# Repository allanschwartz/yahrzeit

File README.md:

# Yahrzeit Project Introduction

*The operator interface and Linux appliance calculate and schedule memorial
lighting, while the embedded controller drives the physical Yahrzeit Wall.*

This repository contains the full Yahrzeit Wall system for Congregation Beth Sholom: the web appliance, scheduling logic, embedded controller firmware, LED hardware designs, and supporting documentation.

## What the project does

The system tracks memorial (Yahrzeit) records, determines when lights should be on, and sends commands to the physical wall so that the correct LEDs illuminate at the correct times.

## Repository layout

- `yahrzeit_site-v3/` — current PHP web application for viewing and editing memorial records, configuring synagogue policy, and running reports.
- `yahrzeit_site-v2/` — earlier web site implementation.
- `embedded/` — firmware and controller software for the embedded wall controller.
  - `yahrzeit_v1/` — original controller implementation.
  - `yahrzeit_v2/` — Arduino-based development work.
  - `yahrzeit_v3/` — newer controller and threading-based implementation.
- `Hardware/` — PCB and enclosure design files, schematics, and related hardware documentation.
- `panels/` — stored panel layouts and panel master assets used by the display system.
- `presentations/` — presentation materials and images related to the project.

## System overview

1. The web application stores memorial data and synagogue settings.
2. The scheduling/engine logic decides which names and panels should be lit.
3. The embedded controller receives commands and drives the LED wall.
4. The hardware layer defines the pixel boards, wiring, and panel geometry.

## Key concepts

- **Yahrzeit Wall** — the physical LED display.
- **Yahrzeit Appliance** — the software environment used by operators to manage the wall.
- **Embedded Controller** — the controller that talks to the LEDs.
- **Pixel Board / Light Engine** — the physical LED modules that make up the display.
- **Minhag / Lighting Policy** — synagogue-specific rules that determine when observances are active.

## Notes for contributors

- The current web application lives under [yahrzeit_site-v3](yahrzeit_site-v3).
- The embedded controller work is separate from the PHP appliance and should be treated as its own hardware/software subsystem.
- If you are updating documentation, prefer clear, project-level explanations that describe how the pieces fit together.

## See Also

- **Project**
  - [`./README.md`](README.md)
- **Server**
  - [`./yahrzeit_site-v3/README.md`](yahrzeit_site-v3/README.md)
  - [`./yahrzeit_site-v3/INSTALL.md`](yahrzeit_site-v3/INSTALL.md)
- **Controller**
  - [`./embedded/yahrzeit_v3/README.md`](embedded/yahrzeit_v3/README.md)
  - [`./embedded/yahrzeit_v3/INSTALL.md`](embedded/yahrzeit_v3/INSTALL.md)
- **Hardware**
  - [`./Hardware/README.md`](Hardware/README.md)

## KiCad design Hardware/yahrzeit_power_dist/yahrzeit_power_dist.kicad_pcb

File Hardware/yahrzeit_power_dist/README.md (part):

# Yahrzeit Wall 5 V Power Distribution Board

## Purpose

This board replaces the improvised low-voltage distribution wiring for one
column of the Yahrzeit Wall. One assembly accepts regulated 5 V DC from an
external power supply and distributes it to the six YYZ_PIXEL-board chains in
that column. The main input and every output branch have independent
overcurrent protection.

The complete wall has seven panel columns and therefore requires seven working
assemblies. The pricing basis is nine boards: seven for the
installed columns, and two spares onsite. Fully cabled spare assemblies remain the service objective;
final cable and power-supply quantities depend on how the spares are equipped.

This is a **direct-5 V distribution board**. The external supply, its output-voltage
adjustment, feed cable, and voltage drop under load are therefore part of the
system design.

The design is ready for prototype pricing and mechanical review, but not yet
for an unchecked production order. Complete the measurements and reviews in
[DESIGN_TODO.md](DESIGN_TODO.md) before fabrication.

## Design illustrations

*Direct-5 V input, main fuse, complementary bypass capacitors, power-present
indicator, and six independently protected outputs. Select the image to open
the PDF schematic.*

*The KiCad sources are authoritative; verify connector and cable
clearances with physical parts before release.*

## Electrical overview

- Input: regulated +5 V and GND through two-position terminal
  block J1.
- Main protection: F1 is a replaceable 7.5 A mini blade fuse in a
  PCB-mounted holder.
- Input filtering: C1 / C2 / C3 provide bulk capacitance, mid-frequency
  bypassing, and high-frequency bypassing after F1.
- Distribution: a broad +5 V copper region feeds six output branches.
- Branch protection: resettable PTC fuses F2 through F7 protect outputs J2
  through J7 independently.
- Connectors: J1 through J7 are Phoenix Contact `5442206` (BC-508X10-2 GN),
  two-position 5.08 mm-pitch PCB terminal blocks with horizontal wire entry.
  These connectors use pin 1 for +5 V and pin 2 for GND.
- Power indication: LED1 and R1 indicate that fused +5 V is present. The LED is
  advisory only and is not a safe-to-service interlock.

The front layer contains a shaped `+5V_BUS_PLANE` and a surrounding GND pour.
The back layer is a GND plane. C1, C2, and C3 straddle the +5 V/GND boundary.
The fused 5 V input feeds each branch circuit.

TP1/TP2 sit between the left mounting holes and measure input voltage.
TP3/TP4 sit between the right mounting holes and measure one of the fused output voltages.
LED1, powered through R1 from the fused 5 V rail, is labeled `POWERED`.
The indicator does not establish that all six PTC-protected outputs are live.

## Connector and cable interfaces

| Connector | Function | Pin 1 | Pin 2 |
|---|---|---|---|
| J1 | Regulated 5 V input | +5 V | GND |
| J2–J7 | Protected pixel-chain outputs | +5 V | GND |

Connector polarity must be checked against the board silkscreen, power-supply
terminals, and existing cable conductors before connection.

### J2-J7 existing output leads

Reuse the six existing cables that connect this distribution board to the six
YYZ_PIXEL board chains. At the wire nut or distribution end, cut off the obsolete
wire-nut termination and crimp on a ferrule sized for the conductor.
The [Phoenix 5442206](https://www.phoenixcontact.com/en-us/products/printed-circuit-board-terminal-bc-508x10-2-gn-5442206) specifies a 6 mm stripping length;
select a compatible ferrule and strip to its barrel length, with no exposed
conductor outside the terminal.
Keep each cable's existing pixel-board connector intact. With power disconnected,
confirm polarity with a continuity check to the pixel-board connector; retain
red for +5 V and black for GND before clamping each ferrule into J2-J7.

### J1 supply lead

J1 is a two-position screw-clamp terminal.
The supply wire is a short, approximately 24 inch, two-conductor 18 AWG feed from the
regulated 5 V supply. Terminate the supply end with ferrules compatible with
the supply's captive screw-clamp terminals; use compatible ferrules at J1
as well (four ferrules total). Prepare each end for its terminal and ferrule.
Connector J1 is
the same Phoenix terminal block as used at J2-J7.
Confirm the cable route,
length, ferrule fit, tightening torque, continuity, and polarity
before installation. Measure voltage drop under maximum load before approving
18 AWG for the final length. The power supply output is adjustable by ±10%.

## Mechanical and fabrication intent

- Board outline: 140 mm × 50 mm; outputs spaced at 20 mm centers.
- Board material: 2.0 mm FR-4; KiCad board thickness is set to 2.0 mm.
- Copper weight: 2 oz finished copper selected for the fabrication quote.
- Fabrication: two layers, green solder mask, white silkscreen, lead-free HASL.
- Mounting: four 4.5 mm mounting holes for attachment to plywood, with centers
  7.5 mm from each adjacent edge. Mount on standoffs to provide clearance beneath the PCB.
- Installation: behind each hinged wall panel, with all connectors and fuses
  accessible for service.

Before final fabrication, verify the board outline, mounting locations, hinge
clearance, connector access, fuse-removal clearance, LED visibility, and cable
bend radius with a full-size print, STEP model, or physical mockup.

## Design files

- `yahrzeit_power_dist.kicad_pro` — KiCad project
- `yahrzeit_power_dist.kicad_sch` — authoritative schematic source
- `yahrzeit_power_dist.kicad_pcb` — authoritative PCB source
- `power_dist_schematic.pdf` — schematic for reviewers without KiCad
- `power_dist_schematic.png` — README rendering of the schematic
- `yahrzeit_power_dist.PCBview.png` — saved PCB layout view
- `yahrzeit_power_dist.3Dview.png` — saved 3D view; verify current terminal
  block models and wire access against physical parts
- `yahrzeit_power_dist.pretty/` — project-specific footprints
- `enclosure/` — parametric wall enclosure and 4 × 8 box alignment jig
- `DESIGN_TODO.md` — remaining validation and release checks

## Component selection / BOM pricing

PCBWay prices are from quotation `T-V40W07135A` dated October 9, 2026,
for nine assembled boards. DigiKey prices are the unit prices in the saved
shopping cart dated October 7, 2026. Prices are per part; quantities are
extended only in the subtotal.

| Designator | Description | Manufacturer part number | Mount | Qty/board | PCBWay unit price (USD) | DigiKey cart unit price (USD) |
|---|---|---|:---:|---:|---:|---:|
| C1 | 470 µF, 25 V, 105 °C, 10,000 h low-impedance aluminum electrolytic bulk capacitor | Rubycon `25ZLH470MEFC10X12.5` | THT radial, 10 mm body, 5 mm pitch | 1 | 0.150 | 0.670 <br>[DigiKey](https://www.digikey.com/en/products/detail/rubycon/25ZLH470MEFC10X12-5/3563614) |
| C2 | 22 µF, 25 V, X7R mid-frequency ceramic bypass capacitor | Cal-Chip `GMC32X7R226K25NT` | SMD 1210 | 1 | 1.633 | 1.350 <br>[DigiKey](https://www.digikey.com/en/products/detail/cal-chip-electronics-inc/GMC32X7R226K25NT/22461278) |
| C3 | 0.1 µF, 50 V, X7R high-frequency ceramic bypass capacitor | Yageo `CC0805KRX7R9BB104` | SMD 0805 | 1 | 0.049 | 0.180 <br>[DigiKey](https://www.digikey.com/en/products/detail/yageo/CC0805KRX7R9BB104/302874?s=N4IgTCBcDaIMJwAwA5EFYDSAlAGgdiwE4AhYgRkQBYQBdAXyA) |
| F1 | 7.5 A, 32 VDC MINI automotive blade fuse | Littelfuse `029707.5WXNV` | Plug-in; purchased separately | 1 | — | 0.301 <br>[DigiKey](https://www.digikey.com/en/products/detail/littelfuse-inc/029707-5WXNV/146586) |
| F1 holder | Vertical MINI blade-fuse PCB holder | Keystone `3568` | THT | 1 | 1.174 | 1.310 <br>[DigiKey](https://www.digikey.com/en/products/detail/keystone-electronics/3568/2137306) |
| F2–F7 | Resettable PTC, 16 V, 1.5 A hold current | Littelfuse `1812L150/16DR` | SMD 1812 | 6 | 0.086 | 0.612 <br>[DigiKey](https://www.digikey.com/en/products/detail/littelfuse-inc/1812L150-16DR/3305611) |
| J1–J7 | PCB terminal block, 2-position, 5.08 mm pitch, horizontal wire entry | Phoenix Contact `5442206` (BC-508X10-2 GN) | THT | 7 | 0.276 | 0.500 est.<br>[DigiKey](https://www.digikey.com/en/products/detail/phoenix-contact/5442206/4390264) |
| LED1 | Green power-present LED | Kingbright `APT2012CGCK` | SMD 0805 | 1 | 0.140 | 0.220 <br>[DigiKey](https://www.digikey.com/en/products/detail/kingbright/APT2012CGCK/1747526) |
| R1 | 1 kΩ, 1%, 0.125 W power-indicator resistor | Yageo `RC0805FR-071KL` | SMD 0805 | 1 | 0.014 | 0.100 <br>[DigiKey](https://www.digikey.com/en/products/detail/yageo/RC0805FR-071KL/727444?s=N4IgTCBcDaIEoGEAMAOJBWAYnAtEg7AIwDSAMiALoC%2BQA) |
| **Installed PCB-component subtotal per board** | | | | | **$5.608** | **$11.002** |

PCBWay's installed-component total is $50.472 for nine boards. The plug-in
fuses are purchased separately and therefore are excluded from both
subtotals. The DigiKey cart reflects the change from Phoenix Contact `1715721`
to `5442206`.

## Extra parts for one complete column assembly

These items are outside the PCB assembly BOM. The existing six pixel-chain
cables are reused for each board; only their board-end terminations are
converted to ferrules. A short supply lead is required for each installed
assembly.

| Item | Description | Part or drawing | Qty/assembly | Unit cost (USD) |
|---|---|---|---:|---:|
| Power supply | Regulated 5 V, 10 A, 50 W adjustable enclosed supply | BTF-LIGHTING `AM50-B05-HD` ([Amazon](https://www.amazon.com/dp/B0FZQNMHN6)) | 1 | $22 |
| Input lead | Two-conductor 18 AWG supply feed, approximately 24 inches; both ends ferruled | n/a | 4 ferrules<br> 24" wire | Negligible—bulk supplies |
| Output lead preparation | Two ferrules per existing J2-J7 cable; six cables are reused | n/a | 12 ferrules | Negligible—bulk supplies |
| 3D printed case | | | | bulk supplies |
| 3mm screws  | with threaded inserts in the case | | | bulk supplies |

The PCB BOM excludes the external 5 V supply, input lead, and ferrules. Bulk and lab supplies will be roughly $50 for the total project.

*Do not release this table as a purchasing BOM until every ordering code,
footprint, voltage/current rating, temperature rating, lifecycle status, and
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
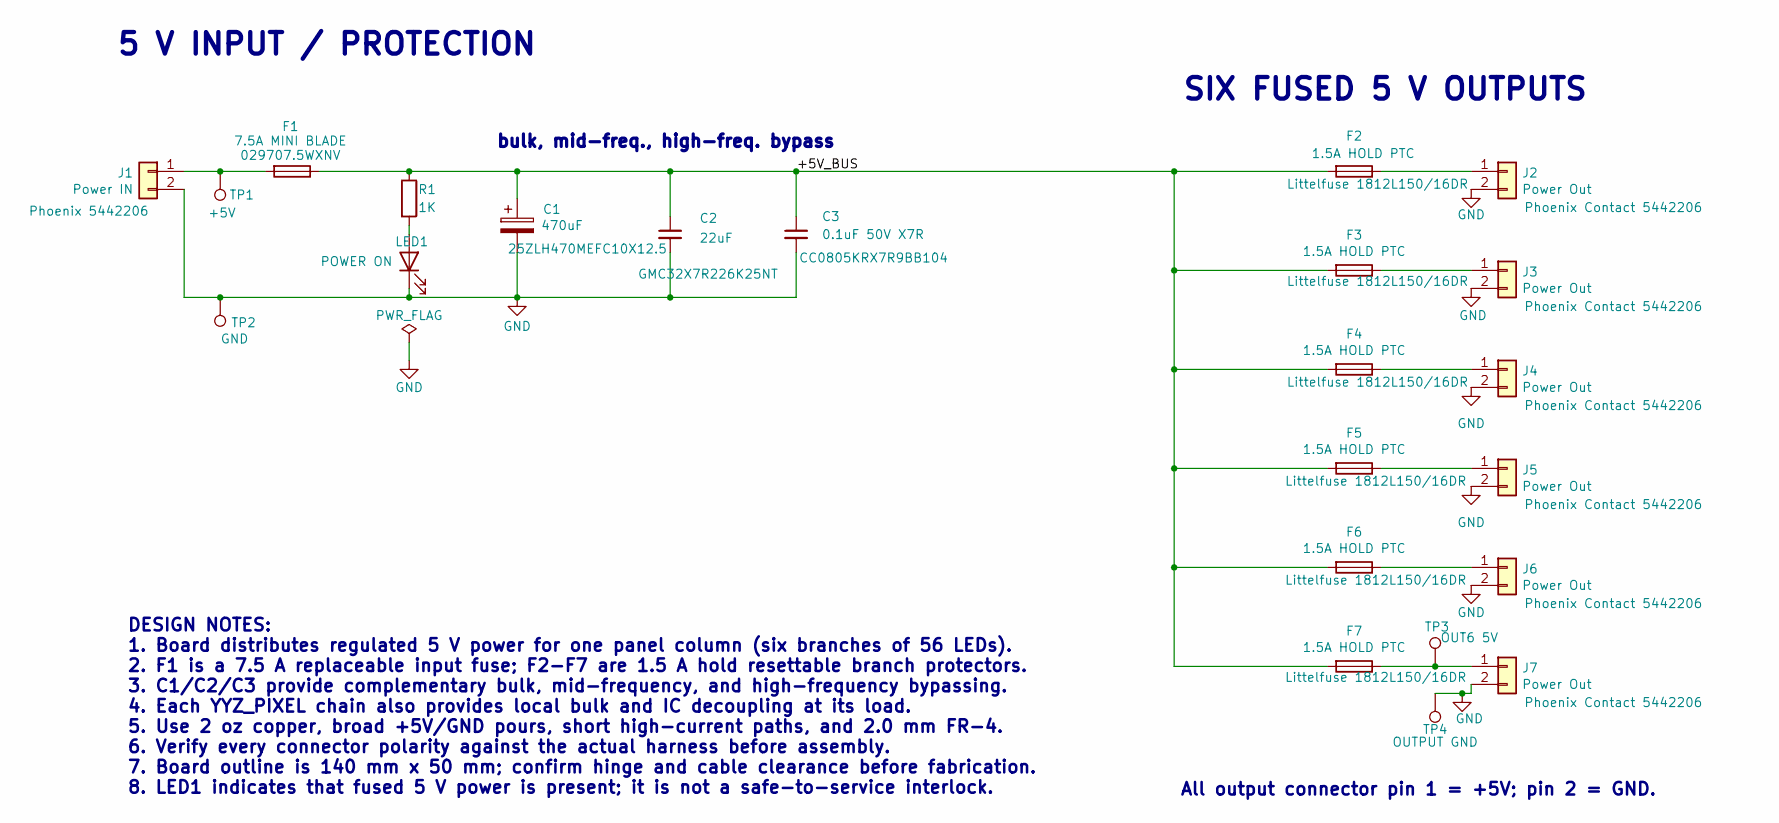
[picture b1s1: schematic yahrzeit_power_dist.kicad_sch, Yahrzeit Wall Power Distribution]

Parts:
C1: 470uF; CP_Radial_D10.0mm_P5.00mm; MPN 25ZLH470MEFC10X12.5
C2: 22uF; C_1210_3225Metric; MPN GMC32X7R226K25NT
C3: 0.1uF 50V X7R; C_0805_2012Metric; MPN CC0805KRX7R9BB104
F1: 7.5A MINI BLADE; Fuseholder_Blade_Mini_Keystone_3568; MPN 029707.5WXNV
F2, F3, F4, F5, F6, F7: 1.5A HOLD PTC; Fuse_1812_4532Metric; MPN Littelfuse 1812L150/16DR
J1: Power IN; TerminalBlock_Phoenix_BC-508X10-2_1x02_P5.08mm_Horizontal; MPN Phoenix 5442206
J2, J3, J4, J5, J6, J7: Power Out; TerminalBlock_Phoenix_BC-508X10-2_1x02_P5.08mm_Horizontal; MPN Phoenix Contact 5442206
LED1: POWER ON; LED_0805_2012Metric; MPN APT2012CGCK
R1: 1K; R_0805_2012Metric; MPN RC0805FR-071KL
TP1: +5V; TestPoint_Pad_D2.5mm; MPN PCB test pad
TP2: GND; TestPoint_Pad_D2.5mm; MPN PCB test pad
TP3: OUT6 5V; TestPoint_Pad_D2.5mm; MPN PCB test pad
TP4: OUTPUT GND; TestPoint_Pad_D2.5mm; MPN PCB test pad

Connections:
/+5V_BUS: C1.1, C2.1, C3.1, F1.1, F2.2, F3.2, F4.2, F5.2, F6.2, F7.2, R1.1
GND: C1.2, C2.2, C3.2, J1.2, J2.2, J3.2, J4.2, J5.2, J6.2, J7.2, LED1.1 (K), TP2.1 (1_1), TP4.1 (1_1)
unnamed: F1.2, J1.1, TP1.1 (1_1)
unnamed: F2.1, J2.1
unnamed: F3.1, J3.1
unnamed: F4.1, J4.1
unnamed: F5.1, J5.1
unnamed: F6.1, J6.1
unnamed: F7.1, J7.1, TP3.1 (1_1)
unnamed: LED1.2 (A), R1.2

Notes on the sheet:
SIX FUSED 5 V OUTPUTS
5 V INPUT / PROTECTION
bulk, mid-freq., high-freq. bypass
All output connector pin 1 = +5V; pin 2 = GND.
DESIGN NOTES: 1. Board distributes regulated 5 V power for one panel column (six branches of 56 LEDs). 2. F1 is a 7.5 A replaceable input fuse; F2-F7 are 1.5 A hold resettable branch protectors. 3. C1/C2/C3 provide complementary bulk, mid-frequency, and high-frequency bypassing. 4. Each YYZ_PIXEL c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

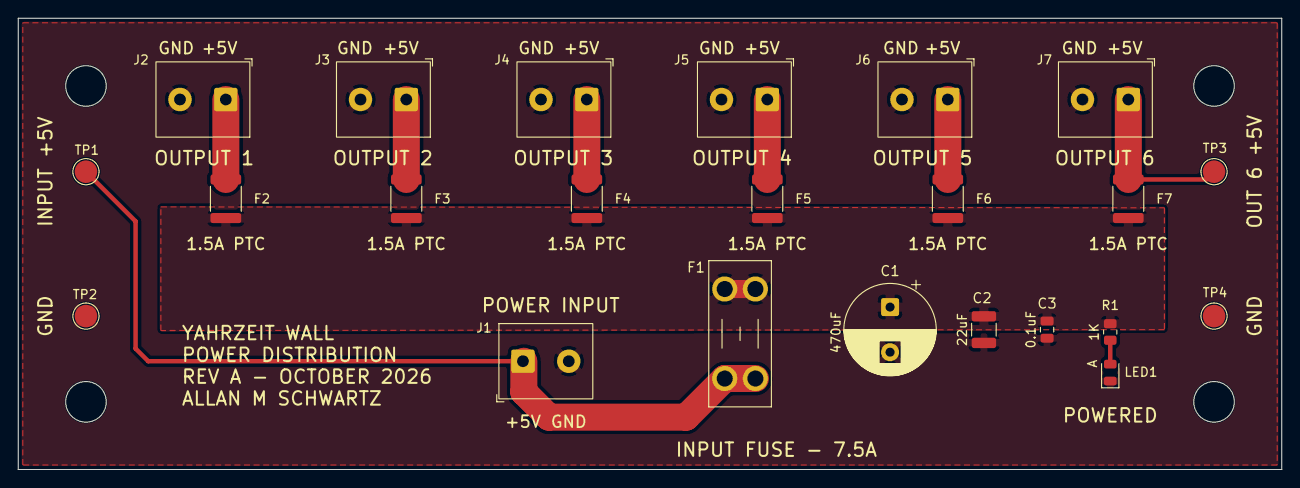
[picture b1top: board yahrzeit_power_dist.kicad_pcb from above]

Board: 2 copper layers, 140.0 x 50.0 mm, 27 parts (0 on the bottom side), 10 nets.

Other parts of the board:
H1, H2, H3, H4: MountingHole_4.5mm

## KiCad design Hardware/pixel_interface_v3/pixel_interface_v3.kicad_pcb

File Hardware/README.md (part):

# Yahrzeit Wall Hardware

This directory contains the electrical and mechanical design files for the
Yahrzeit Wall controller, interface board, pixel boards, test fixtures, and
enclosures.

The current controller uses an Arduino Uno R4, an Arduino-compatible Ethernet
shield, and the Yahrzeit Controller Pixel Interface V3 board. The interface
board connects the controller stack to the installed chain of YYZ Pixel boards.

*The bench-test fixture brings together the controller stack, Pixel Interface
board, and two nine-section YYZ Pixel boards.*

## 3D-Printed Parts

The files under [`3D Printing`](3D%20Printing/) may be browsed
online, with GitHub displaying the JPEG photographs and interactive previews of
the STL models.

### Commercial Controller Enclosure

- [arduino\_uno\_r4\_commercial\_enclosure\_vendor.jpg](3D%20Printing/arduino_uno_r4_commercial_enclosure_vendor.jpg)
  -- Vendor product photograph, saved from the Amazon listing, showing the
  commercial enclosure with an Arduino Uno R4 and an Ethernet-shield stack.

### Production Mounting Flange

The production controller uses a commercial enclosure with a custom
3D-printed flange that adapts its DIN-rail mounting feature for flat wall
mounting.

- [mount\_flange.scad](3D%20Printing/mount_flange.scad) -- Parametric OpenSCAD
  source.
- [mount\_flange.stl](3D%20Printing/mount_flange.stl) -- Printable mounting
  flange.

### Alternative Controller Enclosure

This enclosure was designed for the three-board controller stack. The
close-fitting commercial enclosure documented in the embedded-controller
installation notes is the preferred production enclosure, but this printable
design is retained as a replacement option and design reference.

- [yahrzeit\_controller\_case.scad](3D%20Printing/yahrzeit_controller_case.scad)
  -- Parametric OpenSCAD source.
- [yahrzeit\_controller\_case.stl](3D%20Printing/yahrzeit_controller_case.stl)
  -- Printable enclosure body.
- [yahrzeit\_controller\_case-cover.stl](3D%20Printing/yahrzeit_controller_case-cover.stl)
  -- enclosure cover.
- [yahrzeit\_controller\_case.jpg](3D%20Printing/yahrzeit_controller_case.jpg)
  -- Photograph of the printed enclosure body.

### Test-Fixture Plate

The fixture plate supports the small YYZ Pixel test assembly used during
controller development and bench testing.

- [fixture\_plate.scad](3D%20Printing/fixture_plate.scad) -- Parametric OpenSCAD
  source.
- [fixture\_plate.stl](3D%20Printing/fixture_plate.stl) -- Printable fixture
  plate.
- [fixture\_plate.jpg](3D%20Printing/fixture_plate.jpg) -- Photograph of the
  printed fixture plate.

## Yahrzeit Controller Pixel Interface V3

*KiCad rendering of the Yahrzeit Controller Pixel Interface V3 board.*

The current interface board adapts the Arduino controller stack to the
five-signal YYZ Pixel ribbon cable and provides the green ALIVE status LED.

- [pixel\_interface\_v3.kicad\_pro](pixel_interface_v3/pixel_interface_v3.kicad_pro)
  -- Open this project file in KiCad.
- [pixel\_interface\_v3.kicad\_sch](pixel_interface_v3/pixel_interface_v3.kicad_sch)
  -- KiCad schematic.
- [pixel\_interface\_v3.kicad\_pcb](pixel_interface_v3/pixel_interface_v3.kicad_pcb)
  -- KiCad PCB layout.
- [pixel\_interface\_v3-3D viewer.png](pixel_interface_v3/pixel_interface_v3-3D%20viewer.png)
  -- KiCad 3D rendering.
- [pixel\_interface\_v3-schematic.png](pixel_interface_v3/pixel_interface_v3-schematic.png)
  -- Schematic preview.
- [pixel\_interface\_v3\_D1\_polarity\_note.pdf](pixel_interface_v3/pixel_interface_v3_D1_polarity_note.pdf)
  -- Status-LED polarity and assembly note.

## Nine-Section YYZ Pixel Board

*KiCad rendering of the nine-section YYZ Pixel board.*

The `yahrzeit_pixel9` board combines nine complete YYZ Pixel circuits on one PCB, using the same octal bus transceiver and 8-bit shift register as the individual boards installed in the wall. A single `yahrzeit_pixel9` behaves as one complete Yahrzeit Wall panel, allowing a desktop test fixture to be constructed. Two or more yahrzeit_pixel9 boards may be chained together to emulate multiple panels.

*The reusable KiCad hierarchical sheet implements one eight-pixel YYZ Pixel
circuit. The `yahrzeit_pixel9` top-level schematic instantiates this sheet nine
times.*

- [yahrzeit\_pixel9.kicad\_pro](yahrzeit_pixel9/yahrzeit_pixel9.kicad_pro) --
  Open this project file in KiCad.
- [yahrzeit\_pixel9.kicad\_sch](yahrzeit_pixel9/yahrzeit_pixel9.kicad_sch) --
  KiCad top-level schematic.
- [pblock.kicad\_sch](yahrzeit_pixel9/pblock.kicad_sch) -- Reusable
  eight-pixel hierarchical sheet.
- [yahrzeit\_pixel9.kicad\_pcb](yahrzeit_pixel9/yahrzeit_pixel9.kicad_pcb) --
  KiCad PCB layout.
- [yahrzeit\_pixel9-schematic.pdf](yahrzeit_pixel9/yahrzeit_pixel9-schematic.pdf)
  -- multipage schematic.
- [yahrzeit\_pixel9.png](yahrzeit_pixel9/yahrzeit_pixel9.png) -- KiCad board
  rendering.

## YYZ Pixel Board V2

*Schematic of the preliminary YYZ Pixel Board V2 design.*

YYZ Pixel Board V2 is a proposed modern replacement for an individual
installed pixel board. It retains the legacy 74HC245 input buffer, 74HC595
shift register, 5 V power daisy chain, and 2x5 signal-cable interface so that
it can be evaluated with the existing wall and controller. The present
prototype provides eight LED channels. Its LED resistors intentionally use
four different values, in pairs, so brightness and current can be compared
with the original wall before a production value is selected.

This is design work in progress, not a released production board. Connector
part numbers, the final LED resistor value, cable construction, power margin,
and mechanical fit must be confirmed before fabrication or installation.

- [yahrzeit\_yyz\_pixel-v2.kicad\_pro](yahrzeit_yyz_pixel-v2/yahrzeit_yyz_pixel-v2.kicad_pro)
  -- Open this project file in KiCad.
- [yahrzeit\_yyz\_pixel-v2.kicad\_sch](yahrzeit_yyz_pixel-v2/yahrzeit_yyz_pixel-v2.kicad_sch)
  -- KiCad schematic.
- [yahrzeit\_yyz\_pixel-v2.kicad\_pcb](yahrzeit_yyz_pixel-v2/yahrzeit_yyz_pixel-v2.kicad_pcb)
  -- Preliminary KiCad PCB layout.
- [YYZ\_PIXEL\_V2\_CABLE\_AND\_POWER\_NOTES.md](YYZ_PIXEL_V2_CABLE_AND_POWER_NOTES.md)
  -- Field observations and deferred cable, signal-integrity, and power-design
  decisions.

## Column Power Distribution Board

*KiCad rendering of the 5 V column power-distribution board. Select the image
for the full-size view.*

The power-distribution assembly replaces the wire-nut fan-out for one vertical
panel column. It accepts regulated 5 V from an external 10 A supply through a
two-position screw terminal, protects the input with a replaceable 7.5 A fuse,
and supplies six 56-LED branches through independent 1.5 A resettable fuses.
The screw terminals accept ferrules on the existing output cables, making the
assembly easier to install, diagnose, and replace without connector crimping
tools.

The board is 140 × 50 mm and uses 2 oz finished copper. Ten PCBs and assembly
of nine boards have been ordered: one assembly for each of the wall's seven
panel columns and two onsite spares. A parametric 3D-printed enclosure and an
alignment jig are being developed while the first article is fabricated.

- [yahrzeit\_power\_dist.kicad\_pro](yahrzeit_power_dist/yahrzeit_power_dist.kicad_pro)
  -- Open this project file in KiCad.
- [yahrzeit\_power\_dist.kicad\_sch](yahrzeit_power_dist/yahrzeit_power_dist.kicad_sch)
  -- KiCad schematic.
- [yahrzeit\_power\_dist.kicad\_pcb](yahrzeit_power_dist/yahrzeit_power_dist.kicad_pcb)
  -- PCB layout.
- [power\_dist.schematic.pdf](yahrzeit_power_dist/power_dist.schematic.pdf) -- Current schematic
  PDF for review without KiCad.
- [yahrzeit\_power\_dist.3Dview.png](yahrzeit_power_dist/yahrzeit_power_dist.3Dview.png)
  -- KiCad 3D rendering.
- [README.md](yahrzeit_power_dist/README.md) -- Electrical, mechanical, BOM,
  fabrication, and installation details.
- [enclosure/](yahrzeit_power_dist/enclosure/) -- Parametric OpenSCAD enclosure,
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
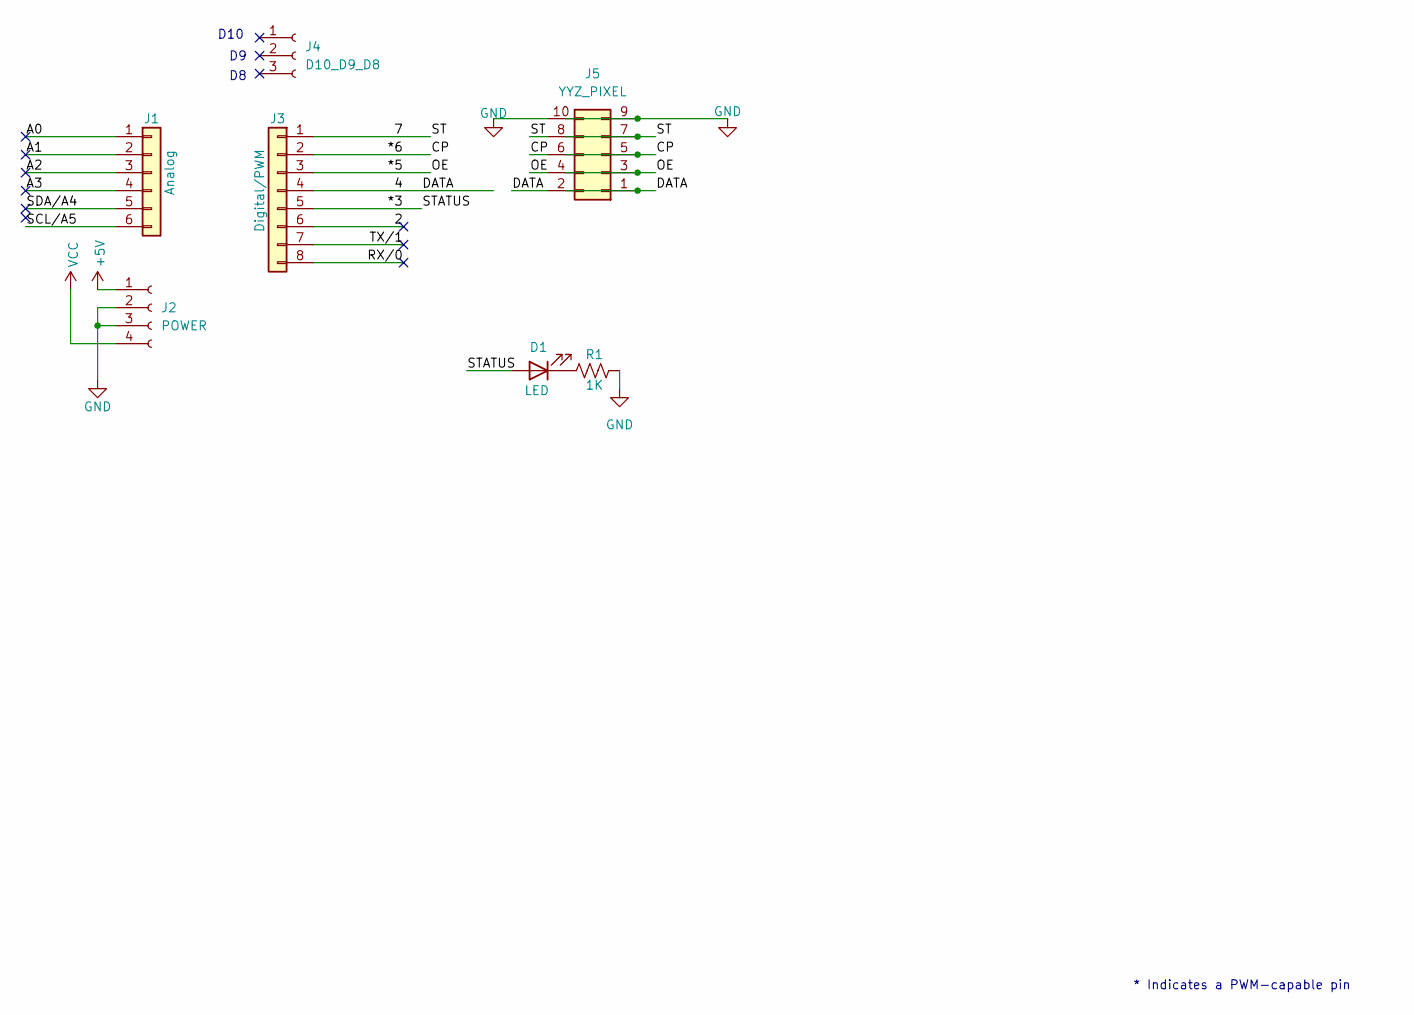
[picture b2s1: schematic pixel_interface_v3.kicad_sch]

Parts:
D1: LED; LED_D3.0mm
J1: Analog; PinSocket_1x06_P2.54mm_Vertical
J2: POWER; PinSocket_1x04_P2.54mm_Vertical
J3: Digital/PWM; PinSocket_1x08_P2.54mm_Vertical
J4: D10_D9_D8; PinSocket_1x03_P2.54mm_Vertical
J5: YYZ_PIXEL; PinHeader_2x05_P2.54mm_Horizontal
R1: 1K; LED_1206_3216Metric_Pad1.42x1.75mm_HandSolder

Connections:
+5V: J2.1
/2: J3.6
/4: J3.4, J5.1, J5.2
/7: J3.1, J5.7, J5.8
/*3: D1.2 (A), J3.5
/*5: J3.3, J5.3, J5.4
/*6: J3.2, J5.5, J5.6
/A0: J1.1
/A1: J1.2
/A2: J1.3
/A3: J1.4
/RX/0: J3.8
/SCL/A5: J1.6
/SDA/A4: J1.5
/TX/1: J3.7
GND: J2.2, J2.3, J5.9, J5.10, R1.2
unnamed: D1.1 (K), R1.1
VCC: J2.4

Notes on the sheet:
* Indicates a PWM-capable pin
D10

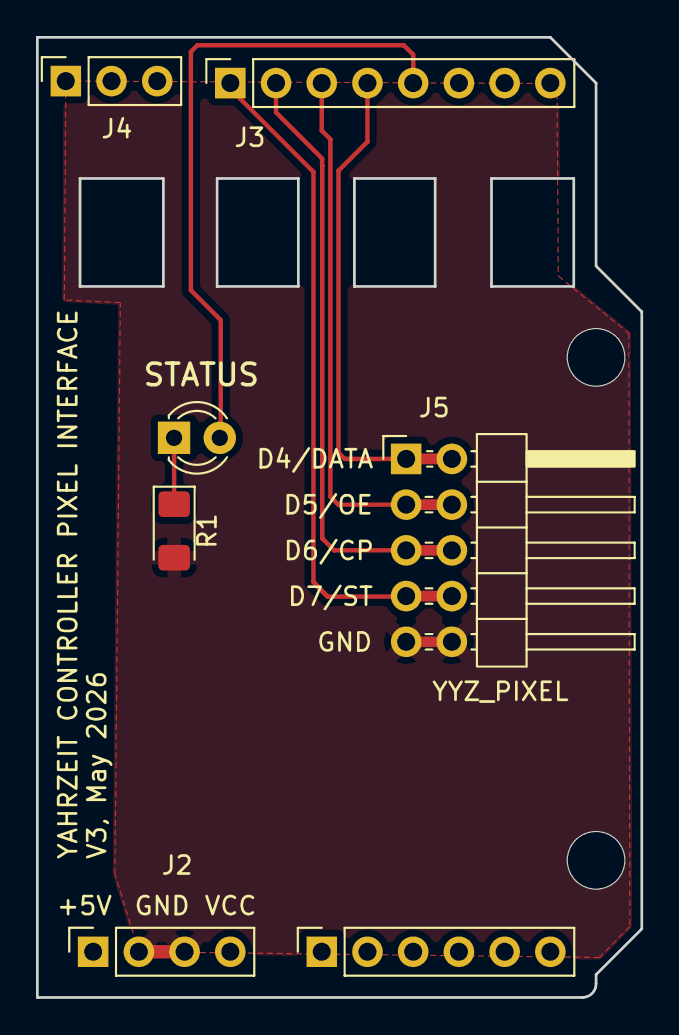
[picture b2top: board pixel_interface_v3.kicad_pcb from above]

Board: 2 copper layers, 33.6 x 53.3 mm, 9 parts (0 on the bottom side), 7 nets.

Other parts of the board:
MH3, MH4: MountingHole_3.2mm

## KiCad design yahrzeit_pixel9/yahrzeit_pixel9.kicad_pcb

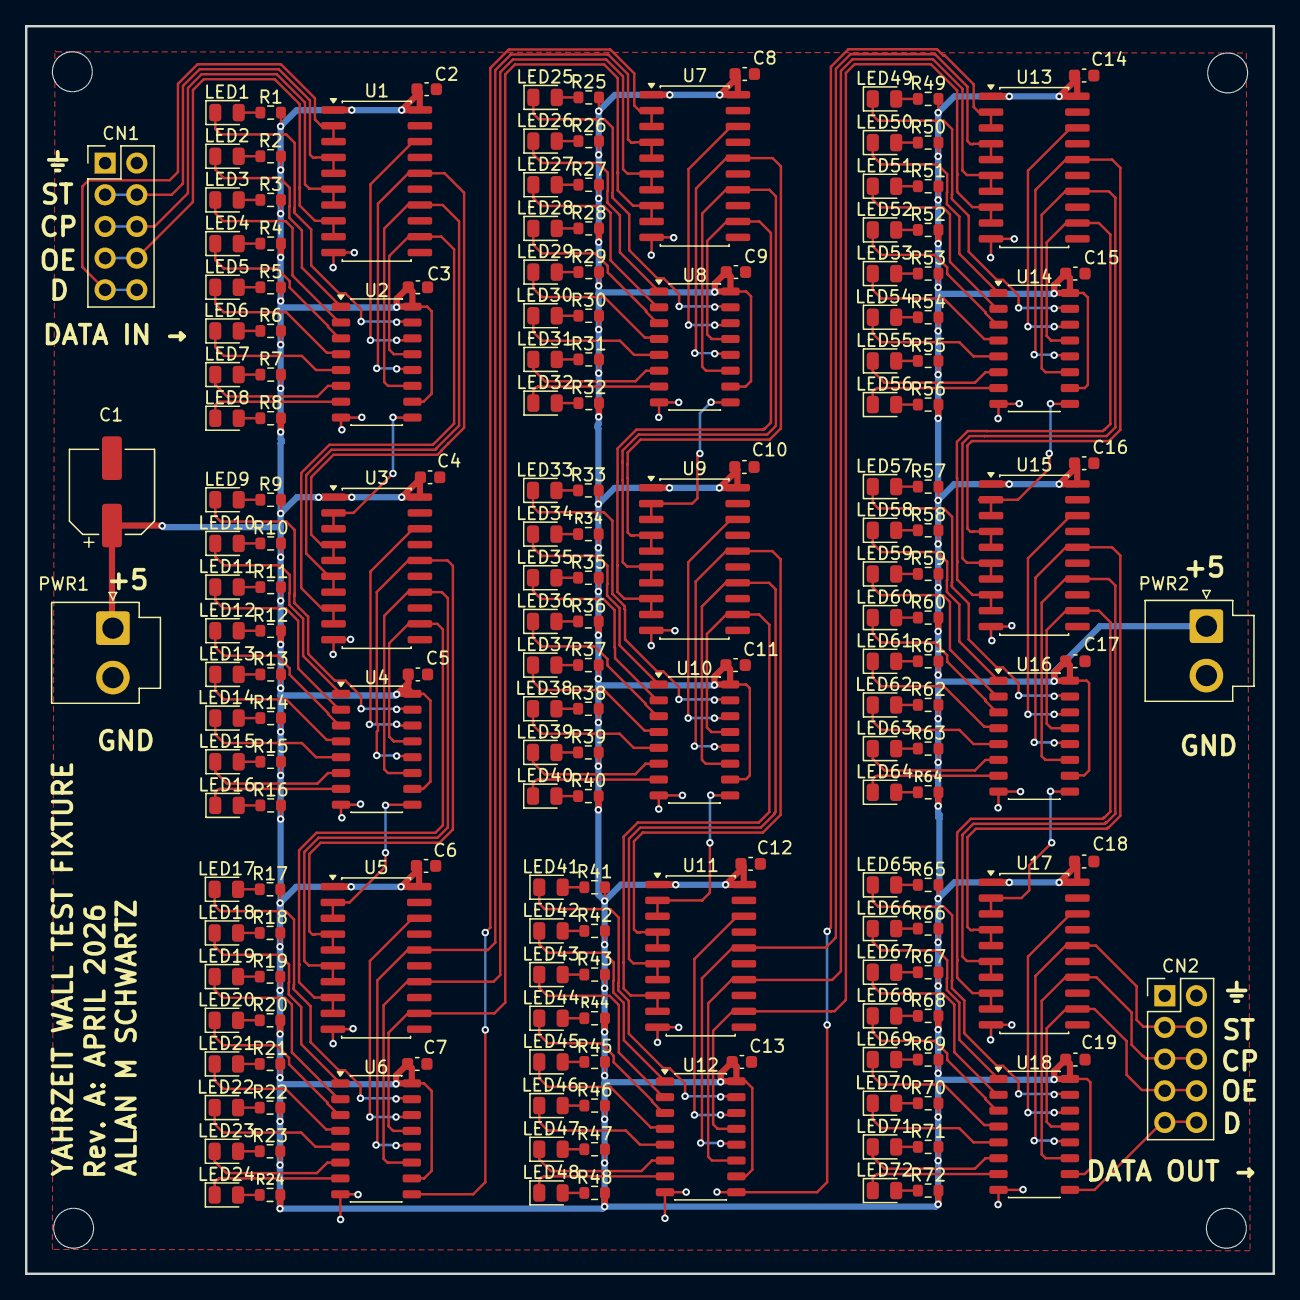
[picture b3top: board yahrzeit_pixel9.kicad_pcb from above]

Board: 2 copper layers, 100.0 x 100.0 mm, 185 parts (0 on the bottom side), 195 nets.

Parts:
C1: 100µF; CP_Elec_6.3x7.7
C2, C3, C4, C5, C6, C7, C8, C9, C10, C11, C12, C13, C14, C15, C16, C17, C18, C19: 0.1µF; C_0603_1608Metric
CN1, CN2: Conn_02x05; PinHeader_2x05_P2.54mm_Vertical
LED1, LED2, LED3, LED4, LED5, LED6, LED7, LED8, LED9, LED10, LED11, LED12, LED13, LED14, LED15, LED16, LED17, LED18, LED19, LED20, LED21, LED22, LED23, LED24, LED25, LED26, LED27, LED28, LED29, LED30, LED31, LED32, LED33, LED34, LED35, LED36, LED37, LED38, LED39, LED40, LED41, LED42, LED43, LED44, LED45, LED46, LED47, LED48, LED49, LED50, LED51, LED52, LED53, LED54, LED55, LED56, LED57, LED58, LED59, LED60, LED61, LED62, LED63, LED64, LED65, LED66, LED67, LED68, LED69, LED70, LED71, LED72: LED; LED_0805_2012Metric
PWR1, PWR2: JST B2P-VH; JST_VH_B2P-VH_1x02_P3.96mm_Vertical
R1, R2, R3, R4, R5, R6, R7, R8, R9, R10, R11, R12, R13, R14, R15, R16, R17, R18, R19, R20, R21, R22, R23, R24, R25, R26, R27, R28, R29, R30, R31, R32, R33, R34, R35, R36, R37, R38, R39, R40, R41, R42, R43, R44, R45, R46, R47, R48, R49, R50, R51, R52, R53, R54, R55, R56, R57, R58, R59, R60, R61, R62, R63, R64, R65, R66, R67, R68, R69, R70, R71, R72: 1k; R_0603_1608Metric
U1, U3, U5, U7, U9, U11, U13, U15, U17: 74HC245; SO-20_5.3x12.6mm_P1.27mm
U2, U4, U6, U8, U10, U12, U14, U16, U18: 74HC595; JEITA_SOIC-16_3.9x9.9mm_P1.27mm

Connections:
/CP4: U5.14 (B4), U6.11 (SRCLK), U7.6 (A4), U7.7 (A5)
/CP7: U11.14 (B4), U12.11 (SRCLK), U13.6 (A4), U13.7 (A5)
/CP_IN: CN1.5, CN1.6, U1.6 (A4), U1.7 (A5)
/CP_OUT: CN2.5, CN2.6, U17.14 (B4), U18.11 (SRCLK)
/DATA4: U6.9 (QH'), U7.2 (A0), U7.3 (A1)
/DATA_IN: CN1.9, CN1.10, U1.2 (A0), U1.3 (A1)
/DATA_OUT: CN2.9, CN2.10, U18.9 (QH')
/OE4: U5.12 (B6), U6.13 (~OE), U7.8 (A6), U7.9 (A7)
/OE7: U11.12 (B6), U12.13 (~OE), U13.8 (A6), U13.9 (A7)
/OE_IN: CN1.7, CN1.8, U1.8 (A6), U1.9 (A7)
/OE_OUT: CN2.7, CN2.8, U17.12 (B6), U18.13 (~OE)
/PB1/CP': U1.14 (B4), U2.11 (SRCLK), U3.6 (A4), U3.7 (A5)
/PB1/DATA': U1.18 (B0), U2.14 (SER)
/PB1/DATA_OUT: U2.9 (QH'), U3.2 (A0), U3.3 (A1)
/PB1/LED1: LED1.1 (K), U2.15 (QA)
/PB1/LED2: LED2.1 (K), U2.1 (QB)
/PB1/LED3: LED3.1 (K), U2.2 (QC)
/PB1/LED4: LED4.1 (K), U2.3 (QD)
/PB1/LED5: LED5.1 (K), U2.4 (QE)
/PB1/LED6: LED6.1 (K), U2.5 (QF)
/PB1/LED7: LED7.1 (K), U2.6 (QG)
/PB1/LED8: LED8.1 (K), U2.7 (QH)
/PB1/OE': U1.12 (B6), U2.13 (~OE), U3.8 (A6), U3.9 (A7)
/PB1/ST': U1.16 (B2), U2.12 (RCLK), U3.4 (A2), U3.5 (A3)
/PB2/CP': U3.14 (B4), U4.11 (SRCLK), U5.6 (A4), U5.7 (A5)
/PB2/DATA': U3.18 (B0), U4.14 (SER)
/PB2/DATA_OUT: U4.9 (QH'), U5.2 (A0), U5.3 (A1)
/PB2/LED1: LED9.1 (K), U4.15 (QA)
/PB2/LED2: LED10.1 (K), U4.1 (QB)
/PB2/LED3: LED11.1 (K), U4.2 (QC)
/PB2/LED4: LED12.1 (K), U4.3 (QD)
/PB2/LED5: LED13.1 (K), U4.4 (QE)
/PB2/LED6: LED14.1 (K), U4.5 (QF)
/PB2/LED7: LED15.1 (K), U4.6 (QG)
/PB2/LED8: LED16.1 (K), U4.7 (QH)
/PB2/OE': U3.12 (B6), U4.13 (~OE), U5.8 (A6), U5.9 (A7)
/PB2/ST': U3.16 (B2), U4.12 (RCLK), U5.4 (A2), U5.5 (A3)
/PB3/DATA': U5.18 (B0), U6.14 (SER)
/PB3/LED1: LED17.1 (K), U6.15 (QA)
/PB3/LED2: LED18.1 (K), U6.1 (QB)
/PB3/LED3: LED19.1 (K), U6.2 (QC)
/PB3/LED4: LED20.1 (K), U6.3 (QD)
/PB3/LED5: LED21.1 (K), U6.4 (QE)
/PB3/LED6: LED22.1 (K), U6.5 (QF)
/PB3/LED7: LED23.1 (K), U6.6 (QG)
/PB3/LED8: LED24.1 (K), U6.7 (QH)
/PB4/CP': U7.14 (B4), U8.11 (SRCLK), U9.6 (A4), U9.7 (A5)
/PB4/DATA': U7.18 (B0), U8.14 (SER)
/PB4/DATA_OUT: U8.9 (QH'), U9.2 (A0), U9.3 (A1)
/PB4/LED1: LED25.1 (K), U8.15 (QA)
/PB4/LED2: LED26.1 (K), U8.1 (QB)
/PB4/LED3: LED27.1 (K), U8.2 (QC)
/PB4/LED4: LED28.1 (K), U8.3 (QD)
/PB4/LED5: LED29.1 (K), U8.4 (QE)
/PB4/LED6: LED30.1 (K), U8.5 (QF)
/PB4/LED7: LED31.1 (K), U8.6 (QG)
/PB4/LED8: LED32.1 (K), U8.7 (QH)
/PB4/OE': U7.12 (B6), U8.13 (~OE), U9.8 (A6), U9.9 (A7)
/PB4/ST': U7.16 (B2), U8.12 (RCLK), U9.4 (A2), U9.5 (A3)
/PB5/CP': U9.14 (B4), U10.11 (SRCLK), U11.6 (A4), U11.7 (A5)
/PB5/DATA': U9.18 (B0), U10.14 (SER)
/PB5/DATA_OUT: U10.9 (QH'), U11.2 (A0), U11.3 (A1)
/PB5/LED1: LED33.1 (K), U10.15 (QA)
/PB5/LED2: LED34.1 (K), U10.1 (QB)
/PB5/LED3: LED35.1 (K), U10.2 (QC)
/PB5/LED4: LED36.1 (K), U10.3 (QD)
/PB5/LED5: LED37.1 (K), U10.4 (QE)
/PB5/LED6: LED38.1 (K), U10.5 (QF)
/PB5/LED7: LED39.1 (K), U10.6 (QG)
/PB5/LED8: LED40.1 (K), U10.7 (QH)
/PB5/OE': U9.12 (B6), U10.13 (~OE), U11.8 (A6), U11.9 (A7)
/PB5/ST': U9.16 (B2), U10.12 (RCLK), U11.4 (A2), U11.5 (A3)
/PB6/DATA': U11.18 (B0), U12.14 (SER)
/PB6/LED1: LED41.1 (K), U12.15 (QA)
/PB6/LED2: LED42.1 (K), U12.1 (QB)
/PB6/LED3: LED43.1 (K), U12.2 (QC)
/PB6/LED4: LED44.1 (K), U12.3 (QD)
/PB6/LED5: LED45.1 (K), U12.4 (QE)
/PB6/LED6: LED46.1 (K), U12.5 (QF)
/PB6/LED7: LED47.1 (K), U12.6 (QG)
/PB6/LED8: LED48.1 (K), U12.7 (QH)
/PB7/CP': U13.14 (B4), U14.11 (SRCLK), U15.6 (A4), U15.7 (A5)
/PB7/DATA': U13.18 (B0), U14.14 (SER)
/PB7/DATA_OUT: U14.9 (QH'), U15.2 (A0), U15.3 (A1)
/PB7/LED1: LED49.1 (K), U14.15 (QA)
/PB7/LED2: LED50.1 (K), U14.1 (QB)
/PB7/LED3: LED51.1 (K), U14.2 (QC)
/PB7/LED4: LED52.1 (K), U14.3 (QD)
/PB7/LED5: LED53.1 (K), U14.4 (QE)
/PB7/LED6: LED54.1 (K), U14.5 (QF)
/PB7/LED7: LED55.1 (K), U14.6 (QG)
/PB7/LED8: LED56.1 (K), U14.7 (QH)
/PB7/OE': U13.12 (B6), U14.13 (~OE), U15.8 (A6), U15.9 (A7)
/PB7/ST': U13.16 (B2), U14.12 (RCLK), U15.4 (A2), U15.5 (A3)
/PB8/CP': U15.14 (B4), U16.11 (SRCLK), U17.6 (A4), U17.7 (A5)
/PB8/DATA': U15.18 (B0), U16.14 (SER)
/PB8/DATA_OUT: U16.9 (QH'), U17.2 (A0), U17.3 (A1)
/PB8/LED1: LED57.1 (K), U16.15 (QA)
/PB8/LED2: LED58.1 (K), U16.1 (QB)
/PB8/LED3: LED59.1 (K), U16.2 (QC)
/PB8/LED4: LED60.1 (K), U16.3 (QD)
/PB8/LED5: LED61.1 (K), U16.4 (QE)
/PB8/LED6: LED62.1 (K), U16.5 (QF)
/PB8/LED7: LED63.1 (K), U16.6 (QG)
/PB8/LED8: LED64.1 (K), U16.7 (QH)
/PB8/OE': U15.12 (B6), U16.13 (~OE), U17.8 (A6), U17.9 (A7)
/PB8/ST': U15.16 (B2), U16.12 (RCLK), U17.4 (A2), U17.5 (A3)
/PB9/DATA': U17.18 (B0), U18.14 (SER)
/PB9/LED1: LED65.1 (K), U18.15 (QA)
/PB9/LED2: LED66.1 (K), U18.1 (QB)
/PB9/LED3: LED67.1 (K), U18.2 (QC)
/PB9/LED4: LED68.1 (K), U18.3 (QD)
/PB9/LED5: LED69.1 (K), U18.4 (QE)
/PB9/LED6: LED70.1 (K), U18.5 (QF)
/PB9/LED7: LED71.1 (K), U18.6 (QG)
/PB9/LED8: LED72.1 (K), U18.7 (QH)
/ST4: U5.16 (B2), U6.12 (RCLK), U7.4 (A2), U7.5 (A3)
/ST7: U11.16 (B2), U12.12 (RCLK), U13.4 (A2), U13.5 (A3)
/ST_IN: CN1.3, CN1.4, U1.4 (A2), U1.5 (A3)
/ST_OUT: CN2.3, CN2.4, U17.16 (B2), U18.12 (RCLK)
/data7: U12.9 (QH'), U13.2 (A0), U13.3 (A1)
GND: C1.2, C2.2, C3.2, C4.2, C5.2, C6.2, C7.2, C8.2, C9.2, C10.2, C11.2, C12.2, C13.2, C14.2, C15.2, C16.2, C17.2, C18.2, C19.2, CN1.1, CN1.2, CN2.1, CN2.2, PWR1.2, PWR2.2, U1.10 (GND), U1.19 (CE), U2.8 (GND), U3.10 (GND), U3.19 (CE), U4.8 (GND), U5.10 (GND), U5.19 (CE), U6.8 (GND), U7.10 (GND), U7.19 (CE), U8.8 (GND), U9.10 (GND), U9.19 (CE), U10.8 (GND), U11.10 (GND), U11.19 (CE), U12.8 (GND), U13.10 (GND), U13.19 (CE), U14.8 (GND), U15.10 (GND), U15.19 (CE), U16.8 (GND), U17.10 (GND), U17.19 (CE), U18.8 (GND)
unnamed: LED1.2 (A), R1.2
unnamed: LED2.2 (A), R2.2
unnamed: LED3.2 (A), R3.2
unnamed: LED4.2 (A), R4.2
unnamed: LED5.2 (A), R5.2
unnamed: LED6.2 (A), R6.2
unnamed: LED7.2 (A), R7.2
unnamed: LED8.2 (A), R8.2
unnamed: LED9.2 (A), R9.2
unnamed: LED10.2 (A), R10.2
unnamed: LED11.2 (A), R11.2
unnamed: LED12.2 (A), R12.2
unnamed: LED13.2 (A), R13.2
unnamed: LED14.2 (A), R14.2
unnamed: LED15.2 (A), R15.2
unnamed: LED16.2 (A), R16.2
unnamed: LED17.2 (A), R17.2
unnamed: LED18.2 (A), R18.2
unnamed: LED19.2 (A), R19.2
unnamed: LED20.2 (A), R20.2
unnamed: LED21.2 (A), R21.2
unnamed: LED22.2 (A), R22.2
unnamed: LED23.2 (A), R23.2
unnamed: LED24.2 (A), R24.2
unnamed: LED25.2 (A), R25.2
unnamed: LED26.2 (A), R26.2
unnamed: LED27.2 (A), R27.2
unnamed: LED28.2 (A), R28.2
unnamed: LED29.2 (A), R29.2
unnamed: LED30.2 (A), R30.2
unnamed: LED31.2 (A), R31.2
unnamed: LED32.2 (A), R32.2
unnamed: LED33.2 (A), R33.2
unnamed: LED34.2 (A), R34.2
unnamed: LED35.2 (A), R35.2
unnamed: LED36.2 (A), R36.2
unnamed: LED37.2 (A), R37.2
unnamed: LED38.2 (A), R38.2
unnamed: LED39.2 (A), R39.2
unnamed: LED40.2 (A), R40.2
unnamed: LED41.2 (A), R41.2
unnamed: LED42.2 (A), R42.2
unnamed: LED43.2 (A), R43.2
unnamed: LED44.2 (A), R44.2
unnamed: LED45.2 (A), R45.2
unnamed: LED46.2 (A), R46.2
unnamed: LED47.2 (A), R47.2
unnamed: LED48.2 (A), R48.2
unnamed: LED49.2 (A), R49.2
unnamed: LED50.2 (A), R50.2
unnamed: LED51.2 (A), R51.2
unnamed: LED52.2 (A), R52.2
unnamed: LED53.2 (A), R53.2
unnamed: LED54.2 (A), R54.2
unnamed: LED55.2 (A), R55.2
unnamed: LED56.2 (A), R56.2
unnamed: LED57.2 (A), R57.2
unnamed: LED58.2 (A), R58.2
unnamed: LED59.2 (A), R59.2
unnamed: LED60.2 (A), R60.2
unnamed: LED61.2 (A), R61.2
unnamed: LED62.2 (A), R62.2
unnamed: LED63.2 (A), R63.2
unnamed: LED64.2 (A), R64.2
unnamed: LED65.2 (A), R65.2
unnamed: LED66.2 (A), R66.2
unnamed: LED67.2 (A), R67.2
unnamed: LED68.2 (A), R68.2
unnamed: LED69.2 (A), R69.2
unnamed: LED70.2 (A), R70.2
unnamed: LED71.2 (A), R71.2
unnamed: LED72.2 (A), R72.2
VCC: C1.1, C2.1, C3.1, C4.1, C5.1, C6.1, C7.1, C8.1, C9.1, C10.1, C11.1, C12.1, C13.1, C14.1, C15.1, C16.1, C17.1, C18.1, C19.1, PWR1.1, PWR2.1, R1.1, R2.1, R3.1, R4.1, R5.1, R6.1, R7.1, R8.1, R9.1, R10.1, R11.1, R12.1, R13.1, R14.1, R15.1, R16.1, R17.1, R18.1, R19.1, R20.1, R21.1, R22.1, R23.1, R24.1, R25.1, R26.1, R27.1, R28.1, R29.1, R30.1, R31.1, R32.1, R33.1, R34.1, R35.1, R36.1, R37.1, R38.1, R39.1, R40.1, R41.1, R42.1, R43.1, R44.1, R45.1, R46.1, R47.1, R48.1, R49.1, R50.1, R51.1, R52.1, R53.1, R54.1, R55.1, R56.1, R57.1, R58.1, R59.1, R60.1, R61.1, R62.1, R63.1, R64.1, R65.1, R66.1, R67.1, R68.1, R69.1, R70.1, R71.1, R72.1, U1.1 (A->B), U1.20 (VCC), U2.10 (~SRCLR), U2.16 (VCC), U3.1 (A->B), U3.20 (VCC), U4.10 (~SRCLR), U4.16 (VCC), U5.1 (A->B), U5.20 (VCC), U6.10 (~SRCLR), U6.16 (VCC), U7.1 (A->B), U7.20 (VCC), U8.10 (~SRCLR), U8.16 (VCC), U9.1 (A->B), U9.20 (VCC), U10.10 (~SRCLR), U10.16 (VCC), U11.1 (A->B), U11.20 (VCC), U12.10 (~SRCLR), U12.16 (VCC), U13.1 (A->B), U13.20 (VCC), U14.10 (~SRCLR), U14.16 (VCC), U15.1 (A->B), U15.20 (VCC), U16.10 (~SRCLR), U16.16 (VCC), U17.1 (A->B), U17.20 (VCC), U18.10 (~SRCLR), U18.16 (VCC)

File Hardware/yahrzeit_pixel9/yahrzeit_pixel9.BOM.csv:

Reference,Qty,Value,Footprint,supplier and part number,Description
C1,1,100µF,Capacitor_SMD:CP_Elec_6.3x7.7,KEMET A768EB107M1ELAS036,CAP ALUM POLY 100UF 20% 25V SMD
"C2,C3,C4,C5,C6,C7,C8,C9,C10,C11,C12,C13,C14,C15,C16,C17,C18,C19",18,0.1µF,Capacitor_SMD:C_0603_1608Metric,NextGen 0603B104K250SD,"CAP,SMD,0603,X7R,0.1UF,10%,25V"
"CN1,CN2",2,Conn_02x05,Connector_PinHeader_2.54mm:PinHeader_2x05_P2.54mm_Vertical,digikey 1849-1002-ND,CONN HEADER VERT 10POS (2x5) 2.54MM
"LED1,LED2,LED3,LED4,LED5,LED6,LED7,LED8,LED9,LED10,LED11,LED12,LED13,LED14,LED15,LED16,LED17,LED18,LED19,LED20,LED21,LED22,LED23,LED24,LED25,LED26,LED27,LED28,LED29,LED30,LED31,LED32,LED33,LED34,LED35,LED36,LED37,LED38,LED39,LED40,LED41,LED42,LED43,LED44,LED45,LED46,LED47,LED48,LED49,LED50,LED51,LED52,LED53,LED54,LED55,LED56,LED57,LED58,LED59,LED60,LED61,LED62,LED63,LED64,LED65,LED66,LED67,LED68,LED69,LED70,LED71,LED72",72,LED,LED_SMD:LED_0805_2012Metric, YY0805RE-NN3S0-T3AR4,LED RED CLEAR 0805 SMD
"PWR1,PWR2",2,JST B2P-VH,Connector_JST:JST_VH_B2P-VH_1x02_P3.96mm_Vertical,JST B2P-VH,"CONN HEADER VERT 2POS 3.96MM, JST VH"
"R1,R2,R3,R4,R5,R6,R7,R8,R9,R10,R11,R12,R13,R14,R15,R16,R17,R18,R19,R20,R21,R22,R23,R24,R25,R26,R27,R28,R29,R30,R31,R32,R33,R34,R35,R36,R37,R38,R39,R40,R41,R42,R43,R44,R45,R46,R47,R48,R49,R50,R51,R52,R53,R54,R55,R56,R57,R58,R59,R60,R61,R62,R63,R64,R65,R66,R67,R68,R69,R70,R71,R72",72,1k,Resistor_SMD:R_0603_1608Metric,RM06F1001CT,RES 1K OHM 1% 1/16W 0603
"U1,U3,U5,U7,U9,U11,U13,U15,U17",9,74HC245,Package_SO:SO-20_5.3x12.6mm_P1.27mm,TI SN74HC245NST,IC TXRX NON-INVERT 6V 20-SO
"U2,U4,U6,U8,U10,U12,U14,U16,U18",9,74HC595,Package_SO:JEITA_SOIC-16_3.9x9.9mm_P1.27mm,Toshiba 74HC595D,IC SR TRI-STATE 8BIT 16-SOIC

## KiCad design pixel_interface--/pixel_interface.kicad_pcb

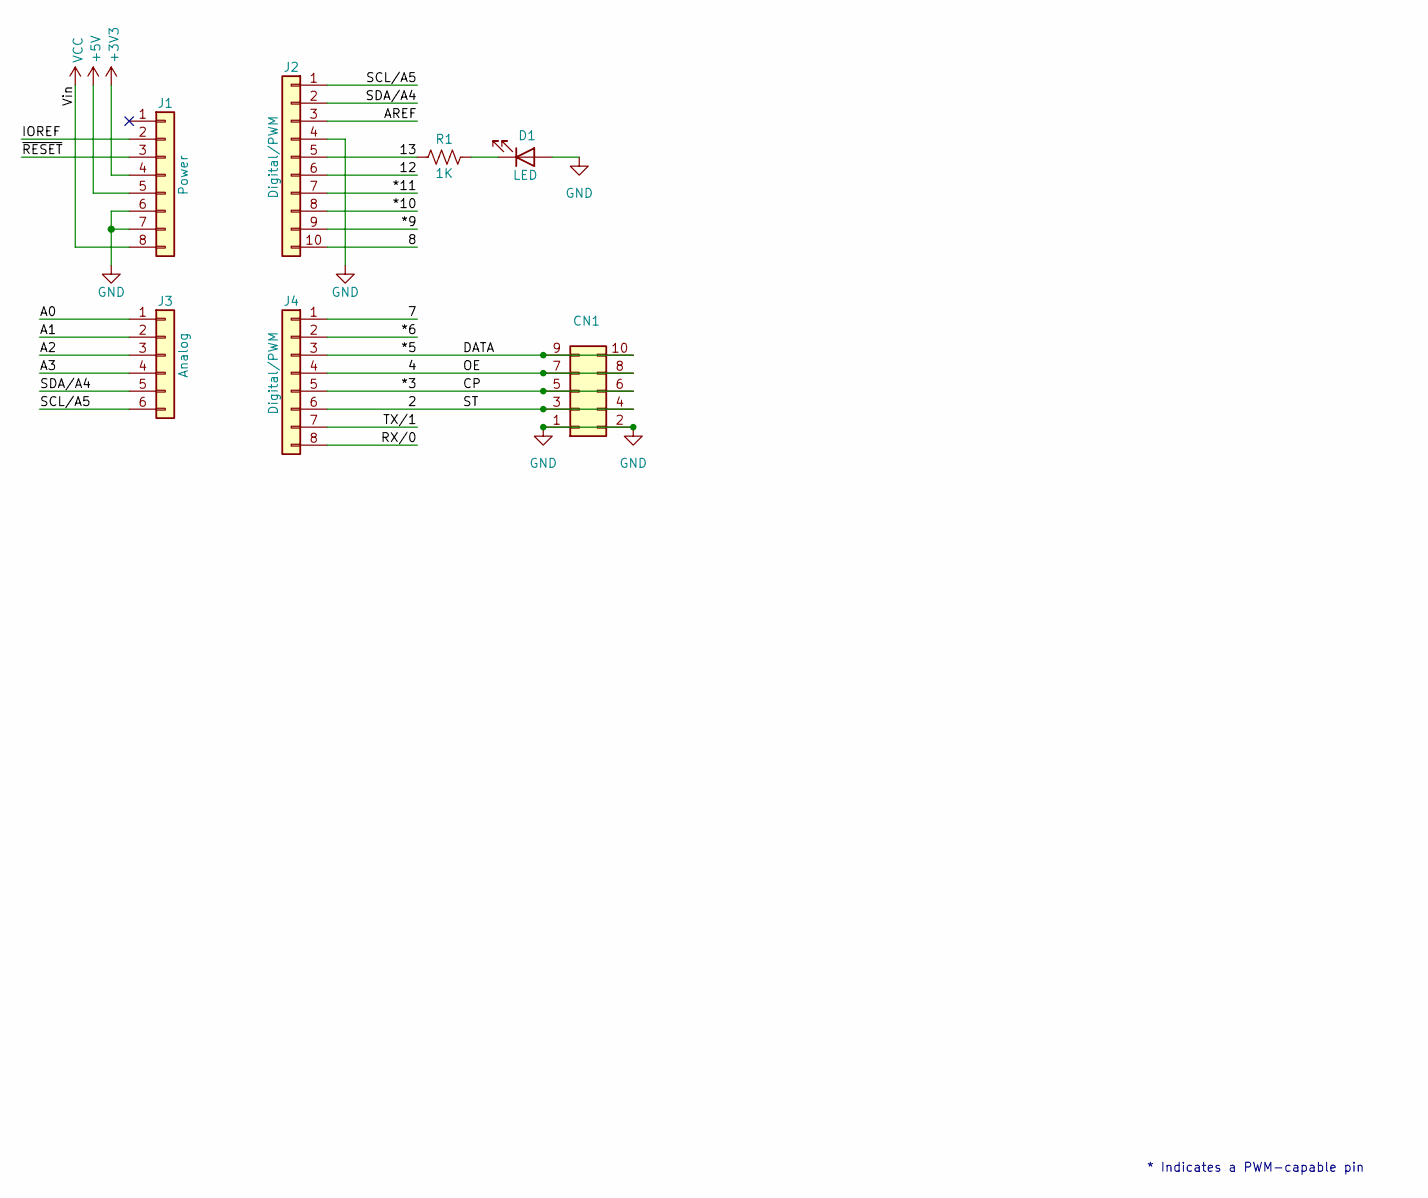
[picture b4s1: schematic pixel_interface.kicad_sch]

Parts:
CN1: Conn_02x05; PinHeader_2x05_P2.54mm_Vertical
D1: LED; R_0603_1608Metric_Pad0.98x0.95mm_HandSolder
J1: Power; PinSocket_1x08_P2.54mm_Vertical
J2: Digital/PWM; PinSocket_1x10_P2.54mm_Vertical
J3: Analog; PinSocket_1x06_P2.54mm_Vertical
J4: Digital/PWM; PinSocket_1x08_P2.54mm_Vertical
R1: 1K

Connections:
+3V3: J1.4
+5V: J1.5
/2: CN1.3, CN1.4, J4.6
/4: CN1.7, CN1.8, J4.4
/7: J4.1
/8: J2.10
/12: J2.6
/13: J2.5, R1.1
/*3: CN1.5, CN1.6, J4.5
/*5: CN1.9, CN1.10, J4.3
/*6: J4.2
/*9: J2.9
/*10: J2.8
/*11: J2.7
/A0: J3.1
/A1: J3.2
/A2: J3.3
/A3: J3.4
/AREF: J2.3
/IOREF: J1.2
/RX/0: J4.8
/SCL/A5: J2.1, J3.6
/SDA/A4: J2.2, J3.5
/TX/1: J4.7
/~RESET: J1.3
GND: CN1.1, CN1.2, D1.2 (A), J1.6, J1.7, J2.4
unnamed: D1.1 (K), R1.2
VCC: J1.8

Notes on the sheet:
* Indicates a PWM-capable pin
